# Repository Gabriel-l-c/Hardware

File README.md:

# Introdução
Este relatório é referente a um projeto de utilização de um  módulo Wireless NRF24L01+ para emitir e receber sinais de rádio que serão computados pelo arduino. Para que a comunicação ocorra corretamente é importante que o canal utilizado entre os módulos esteja entre 2,400 a 2,525 GH

# 1. Metodologia
## 1.1  Pesquisa e documentação
Inicialmente, procurou-se explorar a biblioteca nrf24 produzida para dar suporte a módulos  NRF24L01+  disponibilizada por TMRh20, que já estabelece uma pinagem base para o desenvolvimento do projeto.

## 1.2. Produção do projeto
Com base nos conhecimentos adquiridos na pesquisa da documentação, iniciou-se a produção do projeto físico onde utilizou-se:
2 arduino uno.
2 módulo RF wireless.
3 botões.
LED, buzzers ou displays gráficos.
A configuração física escolhida de pinos está demonstrada nas Figuras 1, 2, 3 e 4. Assim como a configuração final do projeto e o modelo de pinout do módulo na Figura 5.
Importante lembrar que se deve conectar o VCC do módulo em voltagens menores que 5v para evitar que queime.

Figura 1 - Projeto completo já montado com todas pinagens, botões 1,2 e 3 de cima para baixo.

Figura 2 - Arduino receptor de sinal e suas pinagens. 

Figura 3 - Pintagens do arduino transmissor.

Figura 4 - Pinagem de referência geral  dos arduinos.

## 1.3 Testes
Após a finalização do projeto, foi feito o teste e foi observado a sequência de acionamento esperado, 1 botão acende o led vermelho e 2 botões o led verde.
Nota-se que diferentes configurações podem ser facilmente aplicadas ao projeto, como mais leds, algum buzzer ou display para mostrar algum texto, até mesmo um sensor de som ou distância no transmissor para, quando acionados, mandar um sinal para o receptor.

#  Observações

Aparentemente o tratamento de dados do tipo text não é lido corretamente e é printado com erro sendo impossível de ler o resultado.
O pino MISO do módulo dependendo do código, pode atrapalhar envio e recebimento de sinal.
Verificar se o os dois arduino estão conectados no usb do PC(ligados).
Verifique se os pinos estão de acordo com o código.

Dicas dadas:
 Tentar primeiro enviar, receber e printar um valor fixo.
 Tentar “forçar” um fim de vetor para a mensagem enviado e recebida com um”\0” para ver se a mensagem é impressa corretamente. 

## Bibliografia

Eletrogate. Guia Definitivo do Módulo Wireless NRF24L01+. Blog eletrogate. 9 de fevereiro de 2021. Disponível em: 
https://blog.eletrogate.com/guia-definitivo-do-modulo-wireless-nrf24l01-2/. Acesso em: 22 de maio de 2024.

Arduino e cia. Comunicação wireless com Arduino e módulo NRF24L01. Arduino e cia. 19 de fevereiro de 2015. Disponível em: 
https://www.arduinoecia.com.br/comunicacao-wireless-arduino-nrf24l01/. Acesso em: 22 de maio de 2024.

Brendan. RF24. Github, nRF24. 22 de Jul de 2015. Disponivel: <https://github.com/tmrh20/RF24>. Acesso em: 22 de maio de 2024.

TMRh20. Optimized high speed nRF24L01+ driver class documentation. 2020. Disponivel em: <https://nrf24.github.io/RF24/>. Acesso em 23 de maio de 2024.

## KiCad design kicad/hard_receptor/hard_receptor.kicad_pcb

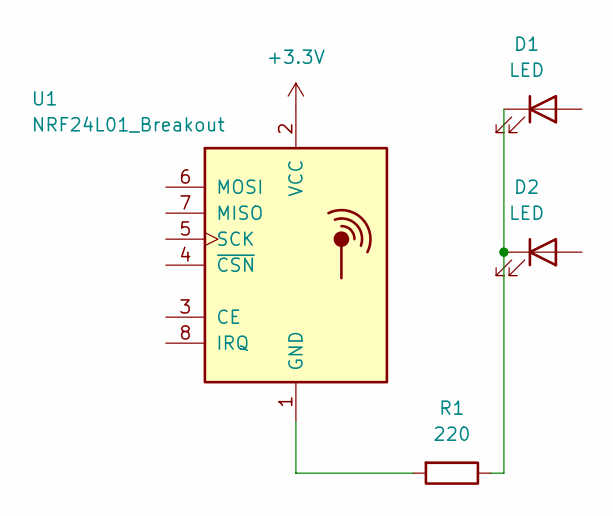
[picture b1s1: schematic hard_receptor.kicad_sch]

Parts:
D1, D2: LED; R_Axial_DIN0204_L3.6mm_D1.6mm_P1.90mm_Vertical
R1: 220; R_Axial_DIN0204_L3.6mm_D1.6mm_P1.90mm_Vertical
U1: NRF24L01_Breakout; nRF24L01_Breakout

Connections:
+3.3V: U1.2 (VCC)
unnamed: D1.1 (K), D2.1 (K), R1.1
unnamed: R1.2, U1.1 (GND)

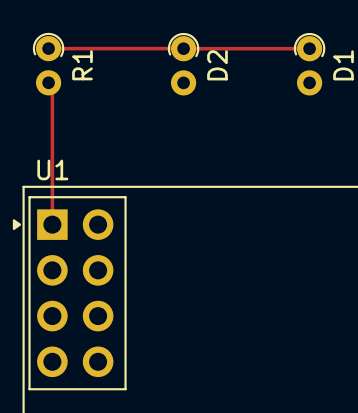
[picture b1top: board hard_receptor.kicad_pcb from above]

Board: 2 copper layers, 4 parts (0 on the bottom side), 2 nets.

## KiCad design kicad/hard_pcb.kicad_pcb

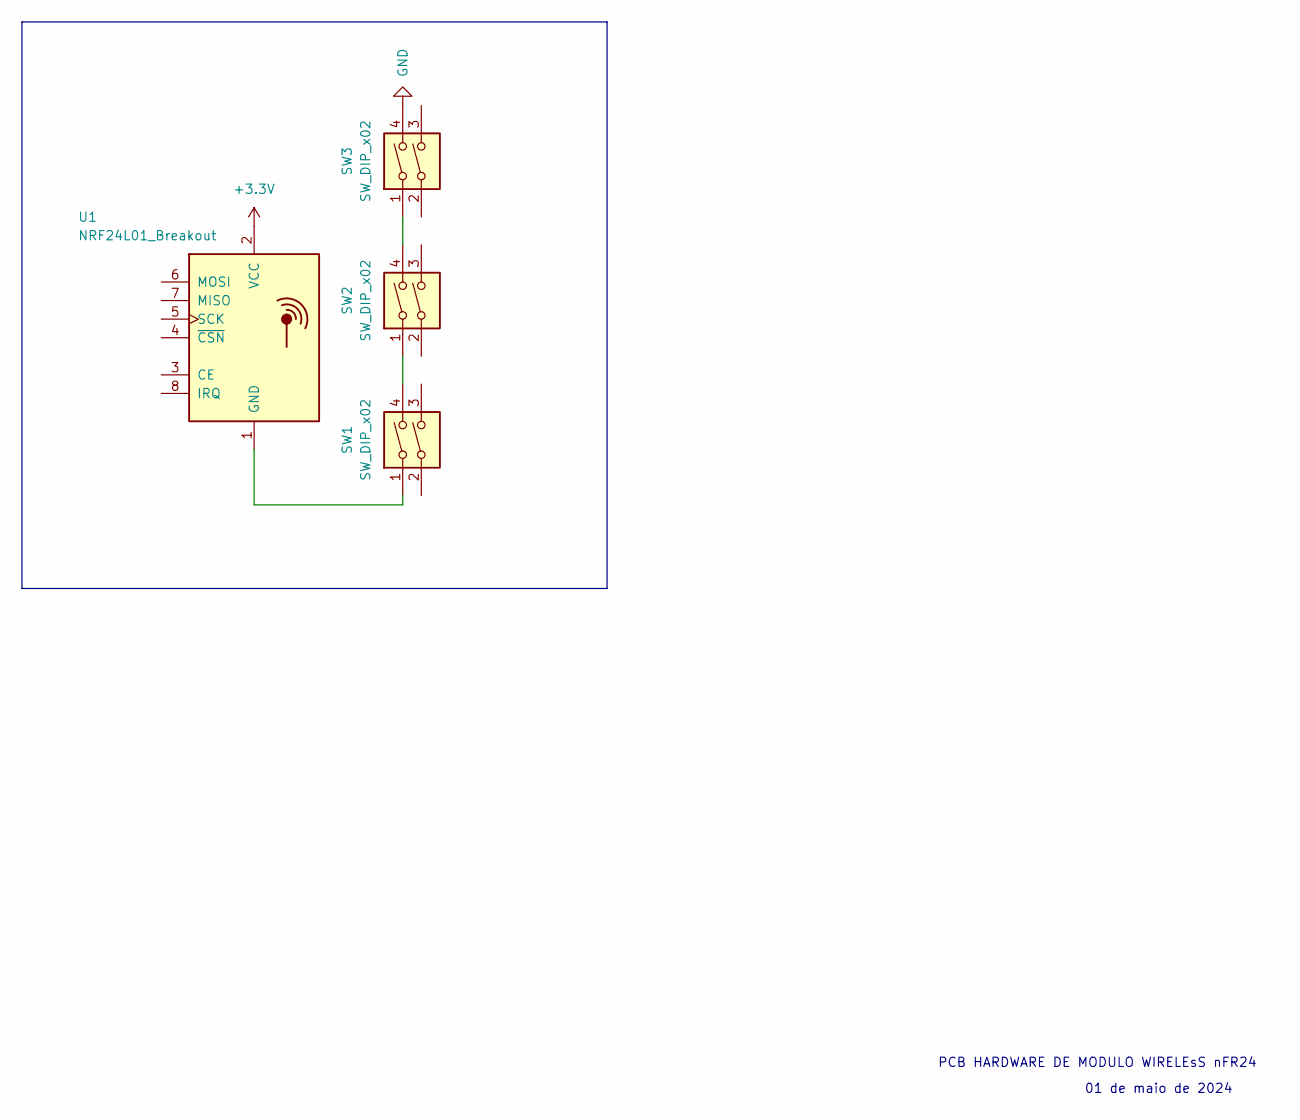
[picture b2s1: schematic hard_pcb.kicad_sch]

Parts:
SW1, SW2, SW3: SW_DIP_x02; SW_DIP_SPSTx02_Slide_9.78x7.26mm_W7.62mm_P2.54mm
U1: NRF24L01_Breakout; nRF24L01_Breakout

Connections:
+3.3V: U1.2 (VCC)
GND: SW3.4
unnamed: SW1.4, SW2.1
unnamed: SW2.4, SW3.1
unnamed: SW1.1, U1.1 (GND)

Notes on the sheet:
01 de maio de 2024
PCB HARDWARE DE MODULO WIRELEsS nFR24

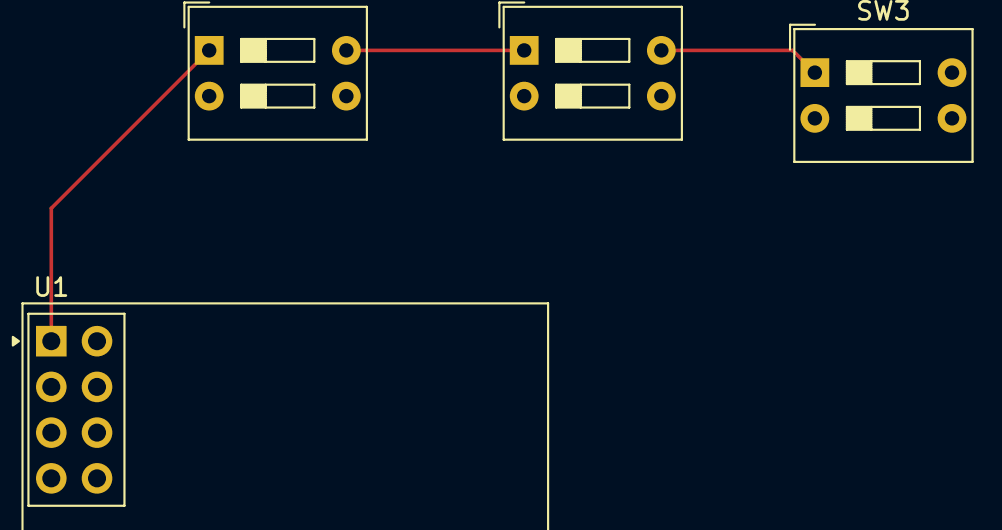
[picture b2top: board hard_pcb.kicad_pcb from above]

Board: 2 copper layers, 4 parts (0 on the bottom side), 3 nets.

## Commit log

2024-05-02 atualizacao de comentarios
2024-05-06 receptor_pcb
